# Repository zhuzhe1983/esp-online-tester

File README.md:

# ESP Online Tester

**Agent-configurable. Human-playable. Embeddable.**

A static platform for complete ESP32 products: select a device, attach accessories, load real firmware, play with its controls, and automate the same session. Forked from [mikroverk/esp32sim](https://github.com/mikroverk/esp32sim); the MIT-licensed Rust emulator runs locally in a browser through WebAssembly.

- [Open the platform](https://zhuzhe1983.github.io/esp-online-tester/platform/)
- [Platform guide and capability boundaries](docs/platform/README.md)
- [Coding-agent skill](skills/esp-online-tester/SKILL.md)
- [Contribute products, accessories and firmware](docs/platform/contributing.md)

Capability labels are product-specific. The [current platform guide](docs/platform/README.md) records implemented peripherals, verified firmware and remaining limits. A preview or successful configuration is not evidence that firmware ran.

The platform lives under `web/platform/`, shares the upstream emulator in `web/wasm/`, and needs no application server. Private DIY accessory definitions stay in the browser unless explicitly exported or shared. Public catalogs accept pull requests.

## LILYGO catalog coverage

The 127 existing LILYGO listings now have source-described 3D previews and newest-first ordering, with hardware dates, provisional storefront dates and unknown dates distinguished. There are 126 executable diagnostic or partial board configurations: 121 added profiles and five existing runtimes. T-Radar remains an A121 expansion module requiring an external host.

The 122 added models use 44 official CAD assemblies or parts and 78 approximate photograph-derived outlines. S2 and C5 currently support explicitly bounded SRAM applications; the P4 display remains a physical preview without DSI frame output. Diagnostic support does not establish factory firmware compatibility or physical model fit. See the [complete chronological inventory, source evidence and validation record](docs/platform/lilygo-adaptation-2026-11-22.md).

## Run locally

```sh
tools/wasm-build.sh
tools/fetch-demo-assets.sh --no-linux
python3 -m http.server 8080 --directory web
# Open http://localhost:8080/platform/
```

See the platform guide for remote firmware manifests, iframe integration, tests, and limitations. The original emulator interface remains available at `run.html`, and its demo gallery at `emulator.html`.

---

## Upstream emulator documentation

# esp32sim

esp32sim is an ESP32 emulator written in Rust. It runs real ESP32 firmware on your computer or in
a browser tab, without the hardware.

It boots the chip's own mask ROM, the real second-stage bootloader and your unmodified application.
It also models the board around the chip: displays, touch, LEDs, buttons, audio, camera and WiFi.

Try it in your browser, nothing to install: https://mikroverk.github.io/esp32sim/

`--chip esp32 --board ai-thinker-cam --cam-image image.ppm` supplies the AI-Thinker
ESP32-CAM's OV2640 with a BMP/PPM still image. Capture supports raw RGB565/YUV422
into internal DRAM at a fixed approximate 10 FPS; the usual JPEG+PSRAM
CameraWebServer path is unsupported. See the [camera scope and example](docs/esp32.md#the-camera---board-ai-thinker-cam).

## Supported chips

| Chip | CPU | Status | Boards |
| --- | --- | --- | --- |
| ESP32-S3 | 2 x Xtensa LX7 | mature | Atech 14-port kit, Waveshare Touch-LCD-4B, Touch-AMOLED-1.8, ESP32-S3-CAM |
| ESP32-S2 | 1 x Xtensa LX7 | SRAM diagnostics | three distinct LILYGO S2 profiles in the WASM platform; no ROM/MMU/SDK boot |
| ESP32-C3 | RISC-V RV32IMC | draft | console only |
| ESP32-C5 | 1 x RISC-V | SRAM diagnostics | Stamp-C5, LILYGO T7-C5 and T-Dongle-C5; no ROM/MMU/SDK boot |
| ESP32-C6 | RISC-V RV32IMAC | draft | Waveshare ESP32-C6-LCD-1.47 (with the 802.15.4 radio), Seeed XIAO ESP32-C6 |
| ESP32 (classic) | 2 x Xtensa LX6 | early | LilyGO TTGO T-Display, ESP32-2432S028 "Cheap Yellow Display", AI-Thinker ESP32-CAM (raw capture), Ulanzi TC001 |
| ESP32-P4 (rev < 3; rev ≥ 3: hello_world, ESP-Hosted) | 2 x RISC-V RV32IMAFC | draft | console only; the C6 co-processor over SDIO |
| ESP32-S31 | 2 x RISC-V RV32IMAFC | draft | native Machine CLI (`--chip s31`); IDF hello_world and ESP-Mosaico; Mosaico V1.2 in the WASM product platform |

S31 supports the native CLI and its `--web` board view, plus ESP-Mosaico V1.2 in
the WebAssembly product platform. The unchanged official Hello 0.1.3 recovery image
boots and responds to touch and AI standby/wake inputs. The publisher currently
blocks browser CORS, so download the complete BIN and import it locally. The model
is photo-derived with UNKNOWN internals; see the [verified scope and limitations](docs/platform/mosaico-runtime.md).
The earlier strict
`Bringup` diagnostic runner and its guest fixtures remain available separately under
`esp32s31::bringup`. See [the board models](docs/boards.md).

## Features

- The full boot chain: mask ROM, bootloader, FreeRTOS, then your app. No patched firmware.
- WiFi with the unmodified Espressif WiFi library. Firmware joins a virtual access point, gets
  DHCP, DNS and NTP, and can reach the real network, HTTPS included.
- Board models, so firmware can draw on a display, read touch, light LEDs and play sound.
- Speed: the S3 has a block cache and a JIT, and runs hello_world about 30 times faster than real
  time.
- A WebAssembly build of the same emulator for the browser.
- Comparisons with real chips: the S3 in JTAG lock-step, the C3 and C6 by console diff. See
  [hardware testing](docs/hardware-testing.md).

## Demos

These run on the [demo site](https://mikroverk.github.io/esp32sim/):

- Linux 6.11 on the ESP32-S3 ([svermigo/Linux-on-esp32-S3](https://github.com/svermigo/Linux-on-esp32-S3)), with a login shell.
- The Atech kit's Pocket Synth and its C64 SID jukebox ([atech-firmware](https://github.com/joakimeriksson/atech-firmware)).
- An LVGL touch panel at 480x480 with a SID player.
- [pocket-tank](https://github.com/mediacutlet/pocket-tank), where a small transformer model steers the fish.
- An 802.15.4 energy scanner, and two Contiki-NG motes running RPL/IPv6, on the ESP32-C6.
- MicroPython on a classic ESP32 T-Display.

You can also load your own firmware for any of the chips.

## Quick start

No Rust needed: the [releases](https://github.com/mikroverk/esp32sim/releases) carry prebuilt binaries
for macOS and Linux, and [docs/quick-start.md](docs/quick-start.md) takes your own build from the tarball
to a run in three steps. From a checkout:

```sh
cargo build --release
tools/fetch-demo-assets.sh --no-linux       # downloads the mask ROMs, which are not in the repo

FW=web/wasm/fw/public                       # demo firmware included in the repo
./target/release/esp32sim --boot rom --rom web/wasm/fw/esp32s3_rev0_rom.elf \
    --bootloader $FW/atech-bootloader.bin --ptable $FW/atech-ptable.bin --app $FW/atech-firmware.bin \
    --script $FW/atech-script1.txt --wav out.wav --tft-png tft.png --max-seconds 5
```

This boots the Atech synth firmware, plays a short script, and saves the audio to `out.wav` and
the display to `tft.png`. Use `esp32sim-c3`, `esp32sim-c6`, `esp32sim-p4`, `esp32sim-s31` or `--chip esp32` for the other chips.

[Getting started](docs/getting-started.md) covers the rest: your own ESP-IDF builds, each chip,
WiFi, scripts, the browser build and debugging.

## Documentation

- [Quick start](docs/quick-start.md): install the release, fetch the mask ROM, run your own build, read the result
- [Getting started](docs/getting-started.md): running firmware on each chip, WiFi, scripts, the browser build
- [CLI reference](docs/cli.md): every flag, environment variable and output file
- [Boards](docs/boards.md): what each board models, and how to add one
- [Architecture](docs/architecture.md): how the emulator is put together
- [Peripherals](docs/peripherals.md): which hardware blocks are modelled, and how completely
- [Hardware testing](docs/hardware-testing.md): how the emulator is compared with real chips
- [All documents](docs/README.md): chip notes, design decisions and plans

## Contributing

Bug fixes, peripherals, boards and new chips are welcome. [CONTRIBUTING.md](CONTRIBUTING.md) lists
what a pull request needs; these are the same checks CI runs. Security problems go through
[SECURITY.md](SECURITY.md), not the public issue tracker.

## Credits and license

esp32sim is released under the [MIT License](LICENSE).

Authors: Joakim Eriksson, RISE ([@joakimeriksson](https://github.com/joakimeriksson)),
Alice ([@aliceisjustplaying](https://github.com/aliceisjustplaying)) and
Mattia Fiumara, Schematik ([@mfiumara](https://github.com/mfiumara)), together with
[other contributors](https://github.com/mikroverk/esp32sim/graphs/contributors).

The emulator was written from the ESP-IDF register headers, the Xtensa core configuration that
ships with ESP-IDF, the RISC-V specification, the chips' technical reference manuals and observed
firmware behaviour. QEMU was consulted only to confirm instruction semantics; no code was copied.

esp32sim is unofficial and not affiliated with Espressif Systems.

Third-party code, data and demo files keep their own licenses:

- pocket-tank ([mediacutlet/pocket-tank](https://github.com/mediacutlet/pocket-tank), MIT). Its
  bootloader, partition table and app are in `web/wasm/fw/public/` with `pocket-tank-LICENSE.txt`;
  its model is downloaded.
- MicroPython ([micropython.org](https://micropython.org/download/ESP32_GENERIC/), MIT): the
  official ESP32_GENERIC v1.29.0 image used by the T-Display demo, downloaded by
  `tools/fetch-micropython.sh` and not in the repo. The demo's app and filesystem are in
  `examples/ttgo-tdisplay`, with Russ Hughes's st7789py driver and fonts (MIT); the notice is in
  `web/wasm/fw/public/tdisplay-NOTICE.txt`.
- Mask ROM ELFs ([espressif/esp-rom-elfs](https://github.com/espressif/esp-rom-elfs), Apache-2.0),
  downloaded, not in the repo.
- xterm.js ([xtermjs/xterm.js](https://github.com/xtermjs/xterm.js), MIT), downloaded, not in the repo.
- The Linux image ([svermigo/Linux-on-esp32-S3](https://github.com/svermigo/Linux-on-esp32-S3),
  GPL-3.0), downloaded, not in the repo.
- ESP-IDF ADC calibration data (Espressif, Apache-2.0): the curve-fitting coefficients and S3 ADC1
  calibration from #165, in `esp-periph/src/sar_adc.rs`; see `esp-periph/LICENSE-ADC`.

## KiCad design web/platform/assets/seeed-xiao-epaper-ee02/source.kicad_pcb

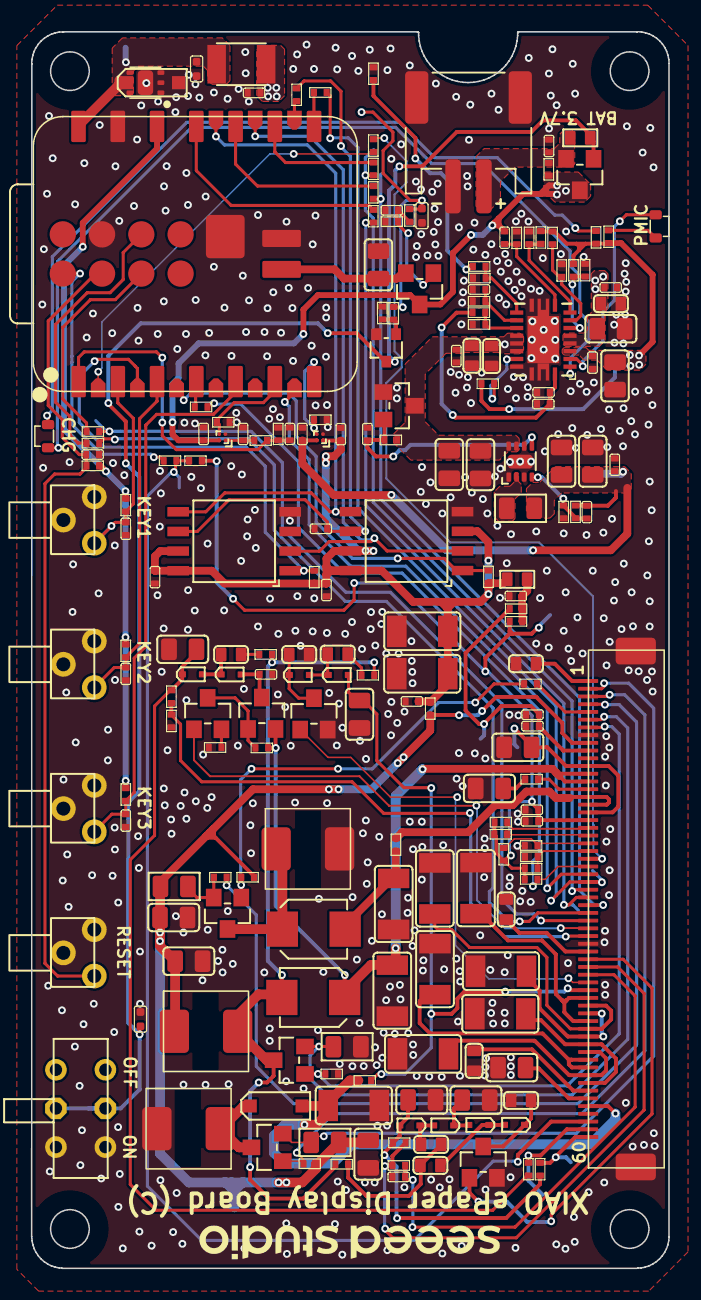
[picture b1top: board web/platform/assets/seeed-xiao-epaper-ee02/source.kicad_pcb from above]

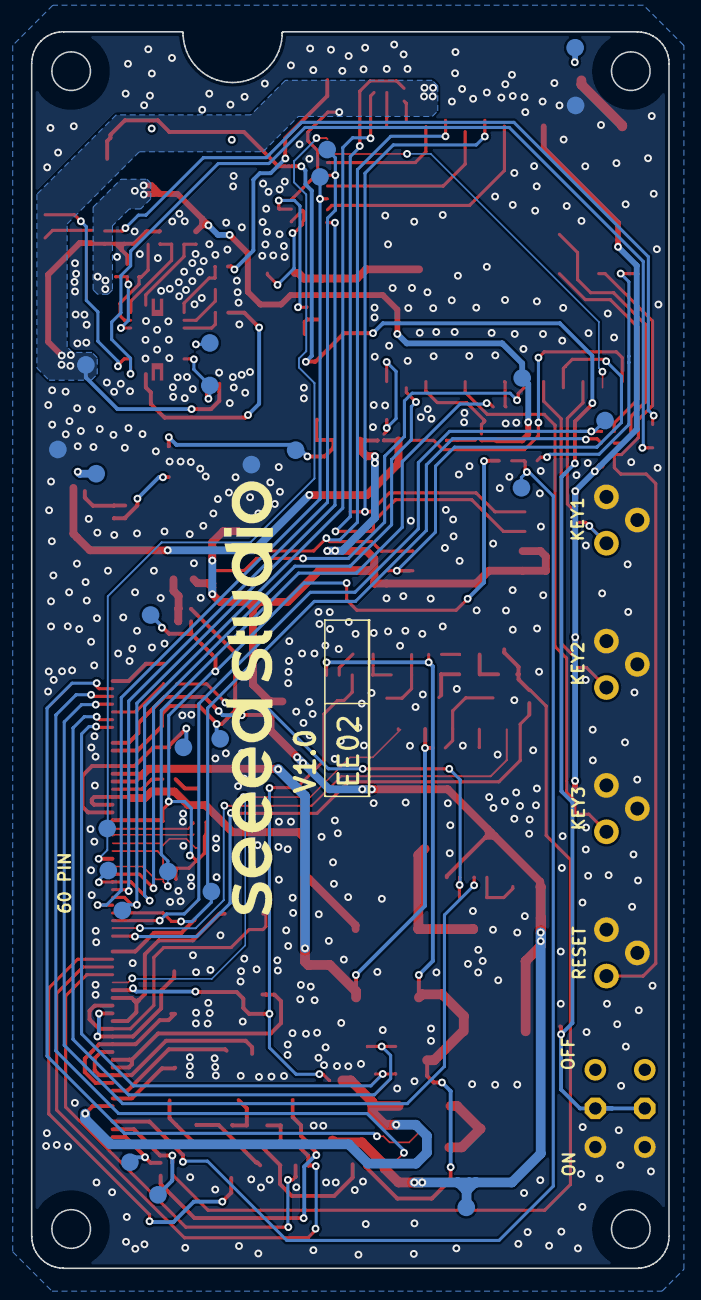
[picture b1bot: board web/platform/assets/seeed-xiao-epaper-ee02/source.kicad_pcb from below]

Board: 2 copper layers, 41.2 x 80.0 mm, 225 parts (25 on the bottom side), 123 nets.

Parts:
C1, C12, C14: 10uF; C1206
C2, C7, C9, C13, C15, C16, C24: 4.7uF,50V; C0805
C3: 470nF; C0402
C4, C20, C23, C28, C36, C44, C49, C50, C51, C53, C54, C55, C56, C58, C61, C63, C64, C71: 100nF; C0402
C5, C68: 100uF; C1206
C6, C8, C17, C19, C27, C52, C66: 470nF; C0603
C10, C21: 47nF; C0603
C11, C40, C41, C42, C43, C60, C72: 10uF; C0805
C18: 1uF; C0805
C22: 220nF,50V; C0402
C25, C39, C46, C47, C48, C59: 1uF; C0402
C26, C29: 10uF; C0402
C30, C31, C32, C33, C34, C65: 47uF,25V; C1206
C35, C70: 22uF; C0805
C37, C38, C57: 10uF; C0603
C45: 22pF; C0402
C62: 1nF; C0402
C67: 220nF; C0402
C69: 10nF; C0402
C73: 47pF; C0402
D1, D3, D6, D7, D8, D9, D10, D11: LRB520S-30T1G; SOD-523
D2, D4: MBRS240LT3; DO-214AA_SMB
D5, D16: Green; LED2-0.6X1.7MM
D12: SMF5.0CA; SOD-123
D13, D14, D15: TPD1E10B06DPYR; ESD-0402
D17: 1N5819HW; SOD-123
F1: 2A; F1210
FB1: MPZ1608S221ATA00; L0603
J1: 130-221-600003-W3G; FPC60-0.5-33.5X4.9X2MM
J3: A2001WF-02A; JST2+2P_2.0_PH_S2B-PH-SM4-TB_1x02-1MP_Horizontal
L2: 0.47uH; L0805
L3, L4, L5: 15uH; L5.5X5.2X3MM
Q1, Q3, Q6, Q10: CJ3407; SOT23
Q2, Q5: 30V 5.8A; SOT23
Q4: LBSS138WT1G; SOT-323
Q7: MMBT3906LT3G; SOT-23
Q8, Q9: 40V,200mA; SOT-23
R1, R6, R55: 1M; R0402
R2, R5, R7, R10, R12, R18, R21, R25, R32, R44, R45, R46, R54, R57, R60, R62, R65, R66, R67: 0R; R0402
R3, R8, R23: 0.2R; R0805
R4, R43, R61, R68, R78: 22R; R0402
R9, R26, R27, R40, R56, R74, R75: 100K; R0402
R11, R17, R19, R28, R29, R30, R31, R35, R36, R37, R38, R39, R63, R64, R70, R71, R72, R73, R76: 10K; R0402
R13, R42, R69: 4.7K; R0402
R14, R15, R47: 2K; R0402
R16, R22: 1K; R0402
R20: NCP15XH103F03RC; R0402
R24: 22K; R0402
R33: 80.6K; R0402
R34: 100K; R0603
R41: 3.57K; R0402
R48: 1.5K; R0402
R49, R51, R53: 2.2R; R0402
R50: 110K; R0402
R52: 16k; R0402
R58: 402K; R0402
R59: 4.3k; R0402
R77: 36K; R0402
SW1: MK-22D18 G3; SW6-2CH-2.54-9X3.5X3.5
SW2, SW3, SW4, SW5: EL-4501V; SW3-DIP-SIDE-4.5X4.5X5.5MM
TP1, TP2, TP3, TP4, TP5, TP6, TP7, TP8, TP9, TP10, TP11, TP12, TP13, TP14, TP15, TP16, TP17, TP18, TP19, TP20, TP21, TP23, TP25, TP26, TP27: Test Point; TP-D45MIL
U1: BQ24070RHLR; RHL20_2P05X3P05
U3: XIAO-HALF-HOLE-33P; XIAO-ESP32-S3-Plus-SMD
U4: ME2805A293XG; SOT-23
U5: ZB25VQ32DSJG; SOIC8-1.27-5.3X5.3MM
U6: GT32L32S0140; SOIC8-1.27-5.3X5.3MM
U7: TVS0500DRVR; WSON7-0.65-2X2X0.8MM
U8: TPS62065DSGR; DFN8G-0.5-2X2MM
U16, U17: TPS22916CYFPR; WLCSP4-0.4-0.77X0.77X0.33MM

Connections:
+3.3V: C42.2, C43.2, C44.1, C45.1, C46.1, L2.2, R56.2, TP6.1 (T), U16.A2 (VIN)
/E-ink/DRVN: J1.37, Q8.1 (B)
/E-ink/DRVN2: J1.40, Q9.1 (B)
/E-ink/DRVP_G: J1.33, Q5.1 (G)
/E-ink/FBN: J1.38, R52.2, R58.1
/E-ink/FBP: J1.34, R50.2, R59.1
/E-ink/GDRC: J1.3, Q6.1 (G), R55.1
/E-ink/GDRN: J1.5, R65.1
/E-ink/GDRP: J1.7, Q2.1 (G), R6.2
/E-ink/LX: D2.1, L5.2, Q2.3 (D), R49.2, R51.2, R53.2
/E-ink/REG_VGN: C25.1, J1.39, R52.1
/E-ink/RESEC: J1.2, Q6.2 (S), R8.1
/E-ink/RESEN: J1.4, R7.1
/E-ink/RESEP: J1.6, Q2.2 (S), R3.2
/E-ink/VBB_3P5V: C12.2, D17.1, J1.56, R57.1
/E-ink/VCC: C11.2, J1.12, J1.18, TP17.1 (T)
/E-ink/VDDN: J1.16, J1.17, R5.2
/E-ink/VDDP: C14.1, D2.2, J1.13, J1.14, Q7.2 (E), R9.1
/E-ink/VGH: J1.59, R66.2, TP16.1 (T)
/E-ink/VGL: J1.60, R67.2, TP15.1 (T)
/E-ink/VNCP_3P5V: C7.2, D11.1, J1.41, R57.2
/XIAO/BUTON1: C54.1, R36.1, SW3.2, U3.2 (GPIO2_D1/A1)
/XIAO/BUTON2: C55.1, R37.1, SW4.2, U3.3 (GPIO3_D2/A2)
/XIAO/BUTON3: C56.1, R38.1, SW5.2, U3.5 (GPIO5_D4/A4/I2C_SDA)
/XIAO/RST: C53.1, R35.1, SW2.2, U3.26 (EN)
/XIAO/SPI1_CLK: C73.1, R78.2, U5.6 (CLK), U6.6 (CLK)
/XIAO/SPI1_CS0: R39.1, U3.16 (GPIO39_CAM_SCL/I2S_SCK), U6.1 (/CS)
/XIAO/SPI1_CS1: R31.1, U3.17 (GPIO40_CAM_SDA/I2S_WS), U5.1 (/CS)
/XIAO/SPI1_MISO: U3.22 (GPIO12_DVP_Y7/SPI_MISO1), U5.2 (DO(IO1)), U6.2 (DO(IO1))
/XIAO/SPI1_MOSI: U3.23 (GPIO13_DVP_PCLK/SPI_SCK1), U5.5 (DI(IO0)), U6.5 (DI(IO0))
ADC_EN: R27.2, U3.6 (GPIO6_D5/A5/I2C_SCL), U17.B2 (EN)
AVDD: C9.2, C13.2, C16.2, J1.9, L5.1, R1.2, R2.2, R8.2, R23.2, R55.2, TP9.1 (T)
BAT_ADC: C62.1, R28.1, R29.2, U3.1 (GPIO1_D0/A0)
EDP_BUSY: J1.25, R47.1, R62.1, TP26.1 (T)
EDP_DC: J1.26, U3.20 (GPIO10_XMCLK/ADC_BAT)
EDP_RST: J1.24, R43.1, TP25.1 (T)
GND: C1.2, C2.1, C3.1, C4.2, C5.2, C7.1, C9.1, C10.2, C11.1, C12.1, C13.1, C14.2, C15.1, C16.1, C18.1, C20.1, C21.2, C22.2, C23.1, C24.1, C25.2, C26.1, C27.1, C28.1, C29.1, C30.1, C31.1, C32.1, C33.1, C34.1, C35.2, C36.2, C37.2, C38.2, C39.2, C40.1, C41.1, C42.1, C43.1, C44.2, C46.2, C47.2, C48.2, C49.2, C50.2, C51.2, C52.1, C53.2, C54.2, C55.2, C56.2, C57.2, C58.2, C59.2, C60.1, C61.2, C62.2, C63.2, C64.2, C65.1, C66.1, C68.2, C69.2, C70.2, C71.2, C72.1, C73.2, D12.1, D13.1, D14.1, D15.1, J1.8, J1.35, J1.61, J1.62, J3.2, J3.3, J3.4, L3.2, L4.2, Q4.2 (S), Q8.2 (E), Q9.2 (E), R3.1, R6.1, R14.2, R15.2, R20.1, R21.1, R24.1, R26.1, R27.1, R29.1, R33.1, R40.1, R41.1, R48.1, R59.2, R71.1, R73.1, R75.1, R76.1, R77.1, SW1.CH1B, SW1.CH2B, SW2.1, SW2.3 (GND), SW3.1, SW3.3 (GND), SW4.1, SW4.3 (GND), SW5.1, SW5.3 (GND), TP4.1 (T), TP5.1 (T), TP8.1 (T), U1.11 (VSS), U1.19 (GND), U1.20 (GND), U1.21 (EPAD), U3.13 (GND), U3.27 (GND1), U3.33 (GND2), U3.34 (PAD), U4.1 (VSS), U5.4 (GND), U6.4 (GND), U7.1 (GND), U7.2 (GND1), U7.3 (GND2), U7.7 (PAD), U8.1 (PGND), U8.3 (AGND), U8.6 (MODE), U8.9 (PAD), U16.B1 (GND), U17.B1 (GND)
unnamed: C1.1, D4.1, R5.1
unnamed: C2.2, D7.1, R58.2, R67.1
unnamed: C6.1, D9.2, D10.1
unnamed: C6.2, R49.1
unnamed: C8.1, D8.1, D11.2
unnamed: C8.2, R53.1
unnamed: C15.2, D10.2, R50.1, R66.1
unnamed: C17.1, D6.1, D7.2
unnamed: C17.2, C19.2, R51.1
unnamed: C18.2, D3.1, D6.2
unnamed: C19.1, D1.1, D3.2
unnamed: C24.2, J1.55
unnamed: C27.2, J1.1
unnamed: C30.2, J1.42, J1.45
unnamed: C31.2, J1.43, J1.46
unnamed: C32.2, J1.49, J1.52
unnamed: C33.2, J1.50, J1.51
unnamed: C34.2, J1.44, J1.47
unnamed: C52.2, J1.54
unnamed: C64.1, FB1.2, R10.1, R12.1
unnamed: C65.2, J1.48, J1.53
unnamed: C66.2, J1.36
unnamed: C72.2, R46.1
unnamed: D5.1 (+), R19.1
unnamed: D5.2 (-), U1.3 (STAT2)
unnamed: D16.1 (+), R17.1
unnamed: D16.2 (-), U1.2 (STAT1)
unnamed: J1.15, R46.2
unnamed: J1.20, R63.2
unnamed: J1.21, R64.2
unnamed: J1.22, R13.1, R14.1
unnamed: J1.23, R15.1, R42.1
unnamed: D4.2, L3.1, Q1.3 (D)
unnamed: Q1.1 (G), R1.1, R65.2
unnamed: Q1.2 (S), R7.2, R23.1
unnamed: D15.2, Q3.1 (G), Q4.3 (D), R34.2, SW1.COM1, SW1.COM2
unnamed: C39.1, J3.1, Q3.2 (S), R32.2, R34.1
unnamed: Q4.1 (G), R16.2, R40.2
unnamed: Q5.3 (D), Q7.1 (B), R9.2
unnamed: Q5.2 (S), R48.2
unnamed: D17.2, L4.1, Q6.3 (D)
unnamed: C22.1, D9.1, Q7.3 (C)
unnamed: C21.1, D1.2, Q8.3 (C)
unnamed: C10.1, D8.2, Q9.3 (C)
unnamed: C59.1, Q10.1 (G), R30.2, R75.2
unnamed: C60.2, Q10.2 (S), U3.32 (VBAT)
unnamed: R18.1, R20.2
unnamed: D12.2, D13.2, F1.1, TP7.1 (T), U3.14 (VBUS), U7.4 (IN), U7.5 (IN2), U7.6 (IN2)
unnamed: R11.1, TP18.1 (T), U1.18 (~PG)
unnamed: C51.1, R25.1, TP20.1 (T), U4.2 (VOUT), U8.5 (EN)
unnamed: R70.2, R71.2, U1.9 (CE)
unnamed: C69.1, R77.2, U1.13 (DPPM)
unnamed: C67.2, R41.2, U1.10 (ISET1)
unnamed: R74.1, R76.2, U1.7 (ISET2)
unnamed: R72.2, R73.2, U1.8 (MODE)
unnamed: R22.2, R33.2, U1.14 (TMR)
unnamed: R18.2, R21.2, U1.12 (TS)
unnamed: R62.2, U3.4 (GPIO4_D3/A3)
unnamed: R4.1, U3.9 (GPIO7_D8/A8/SCK)
unnamed: R44.1, U3.10 (GPIO8_D9/A9/MISO)
unnamed: R45.1, U3.11 (GPIO9_D10/A10/MOSI)
unnamed: R78.1, U3.21 (GPIO11_DVP_Y8/SPI_MOSI1)
unnamed: R43.2, U3.15 (GPIO38_DVP_VSYNC/I2S_SD)
unnamed: R60.1, U3.29 (MTCK/IO39/CAM_SCL/I2S_SCK)
unnamed: R68.1, U3.24 (MTDI/IO41/PDM_DATA/RX1)
unnamed: R54.1, U3.28 (MTMS/IO42/PDM_CLK/TX1)
unnamed: R61.1, U3.8 (U0RXD_D7/RX)
unnamed: C45.2, R24.2, R56.1, U8.4 (FB)
unnamed: L2.1, U8.2 (SW)
unnamed: C49.1, R28.2, U17.A1 (VOUT)
PWR_EN: R26.2, U3.7 (U0TXD_D6/TX), U16.B2 (EN)
SPIO_CLK: J1.28, R4.2, TP10.1 (T)
SPIO_CS_M: J1.27, R61.2, TP27.1 (T)
SPIO_CS_S: J1.58, R68.2, R69.1, TP23.1 (T)
SPIO_D0: J1.29, R45.2, TP11.1 (T)
SPIO_D1: J1.30, R44.2, TP12.1 (T)
SPIO_D2: J1.31, R60.2, TP13.1 (T)
SPIO_D3: J1.32, R54.2, TP14.1 (T)
VBAT: C35.1, C36.1, C37.1, C48.1, C67.1, Q3.3 (D), Q10.3 (D), R32.1, TP3.1 (T), U1.5 (BAT), U1.6 (BAT), U17.A2 (VIN)
VBUS: C58.1, C70.1, C71.1, D14.2, F1.2, R11.2, R16.1, R17.2, R19.2, R30.1, R70.1, R72.1, R74.2, TP21.1 (T), U1.4 (IN)
VCC_3V3: C4.1, C5.1, C47.1, C50.1, C63.1, C68.1, FB1.1, R2.1, R31.2, R39.2, U5.3 (/WP(IO2)), U5.7 (/HOLD(IO3)), U5.8 (VCC), U6.7 (/HOLD(IO3)), U6.8 (VCC), U16.A1 (VOUT)
VDD: C20.2, C26.2, J1.10, R10.2, TP1.1 (T)
VDDIO: C28.2, C29.2, J1.19, R12.2, R13.2, R42.2, R47.2, R63.1, R64.1, R69.2, TP2.1 (T)
VREF: C3.2, C23.2, R22.1, U1.1 (VREF)
VSYS: C38.1, C40.2, C41.2, C57.1, C61.1, R25.2, TP19.1 (T), U1.15 (OUT), U1.16 (OUT), U1.17 (OUT), U4.3 (VIN), U8.7 (AVIN), U8.8 (PVIN)
XIAO_3V3: R35.2, R36.2, R37.2, R38.2, U3.12 (VCC_3V3)

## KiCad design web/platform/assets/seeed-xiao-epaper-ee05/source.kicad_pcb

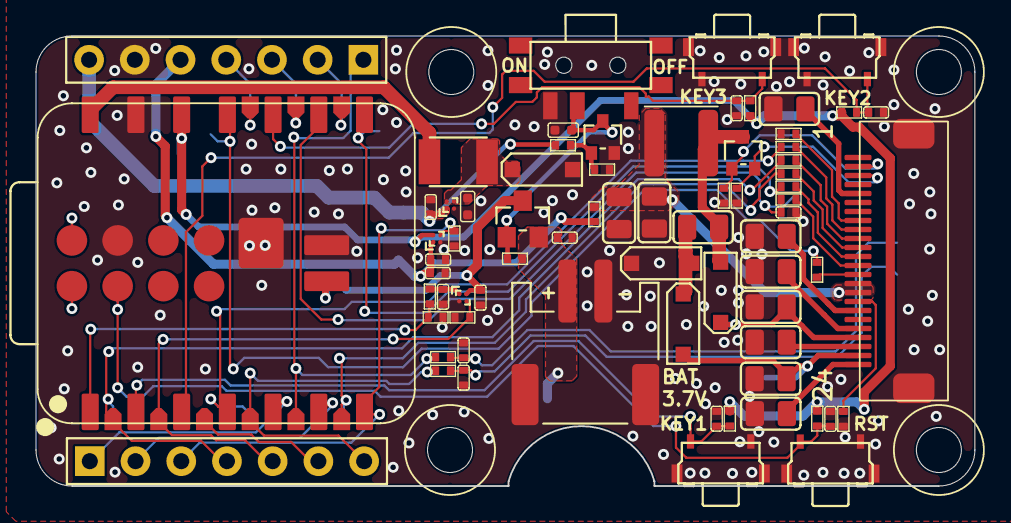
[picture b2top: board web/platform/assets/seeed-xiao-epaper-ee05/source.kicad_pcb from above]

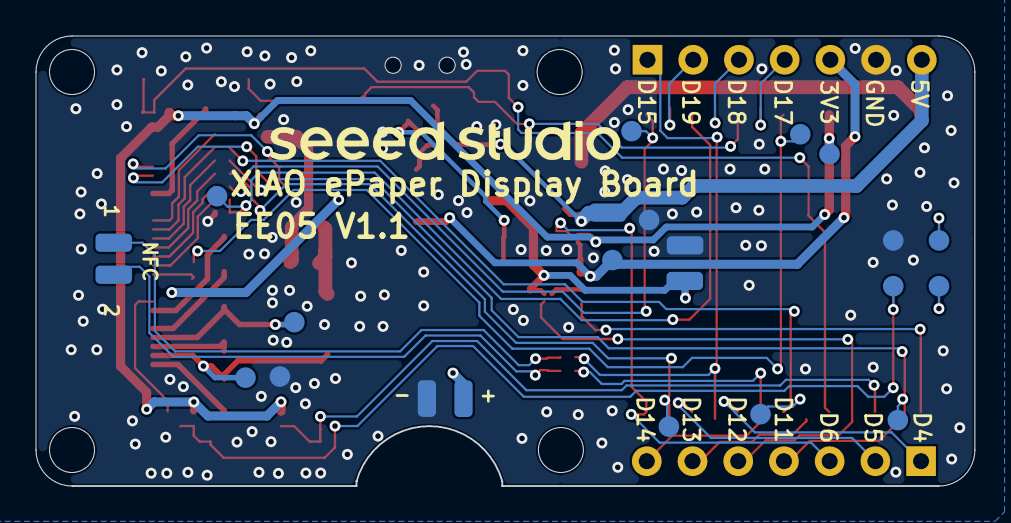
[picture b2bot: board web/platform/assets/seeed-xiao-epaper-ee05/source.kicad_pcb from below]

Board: 2 copper layers, 52.2 x 25.0 mm, 99 parts (23 on the bottom side), 56 nets.

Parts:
C1: 10uF; C0805
C2, C3, C4: 1uF; C0805
C5, C6, C7, C17, C18, C19: 4.7uF; C0805
C8, C9, C11, C12, C13, C14, C15: 100nF; C0402
C10, C16, C20: 1uF; C0402
C21: 33pF; C0402
C64, C65: 300pF; C0402
D1, D2, D3: MBR0530; SOD-123
D6, D15: TPD1E10B06DPYR; ESD-0402
D7: SMF5.0CA; SOD-123
F1: 2A; F1210
J1: FPC 24P TOP contact; FPC24-0.5-15.5X4.9X2MM
J2, J4: ST-PH-254-0087-1*7P-PC1.8; H7-2.54
J3: A2001WF-02A; JST2+2P_2.0_PH_S2B-PH-SM4-TB_1x02-1MP_Horizontal
K1, K2, K3, K4: TD-1100SN-A4N-S1R; SW4-SMD-4.5X3.8X1.8MM-90D
L1: 47uH ±20% 570mA; L4018
Q3: CJ3407; SOT23
Q4: LBSS138WT1G; SOT-323
Q5: 30V-1.4A; SOT-323
R1, R9, R10, R15, R16, R17, R18, R20, R24: 0R; R0402
R2, R4, R11, R21: 1M; R0402
R3, R5, R6, R7, R8, R12, R22, R23: 10K; R0402
R13: 100K; R0402
R14: 2.2R; R0402
R19: 22R; R0402
SW6: MSK-12C02 ZD; SW7-SMD-6.7X2.6X1.4MM-90D
TP1, TP2, TP3, TP4, TP5, TP7, TP8: Test Point; TP-80X40MIL
TP6, TP9, TP10, TP11, TP12, TP13, TP14, TP15, TP16, TP17, TP18, TP19, TP20, TP21, TP22, TP23: Test Point; TP-D45MIL
U1, U2, U6, U7, U8: LOGO_CC_BY-SA_4.0
U3: XIAO-ESP32-S3-Plus-SMD
U4, U5, U9: TPS22916CNYFPR; WLCSP4-0.4-0.77X0.77X0.33MM

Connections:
+3.3V: R5.2, R6.2, R7.2, R8.2, TP6.1 (T_1), U3.12 (3V3_OUT), U4.A2 (VIN)
ADC_EN: J2.5, R21.2, U3.16 (D12), U9.B2 (EN)
BAT_ADC: R22.1, R23.2, U3.1 (D0)
BOTTON1: C13.1, K2.2, R7.1, U3.2 (D1)
BOTTON2: C12.1, K3.2, R6.1, U3.3 (D2)
BOTTON3: C9.1, K4.2, R5.1, U3.10 (D9)
BS1: J1.17, R12.2
EDP_BUSY: R15.1, TP13.1 (T_1), U3.4 (D3)
EDP_DC: R17.1, TP15.1 (T_1), U3.20 (D16)
EDP_RES: J2.4, R16.1, TP14.1 (T_1), U3.15 (D11)
GDR: J1.23, Q5.1 (G), R13.2
GND: C1.2, C2.2, C3.2, C4.2, C5.2, C6.2, C8.2, C9.2, C10.2, C11.2, C12.2, C13.2, C14.2, C15.2, C16.2, C17.2, C18.2, C19.2, C20.2, C21.2, C64.1, C65.2, D2.2, D6.1, D7.1, D15.1, J1.25, J1.26, J3.2, J3.3, J3.4, J4.6, K1.1, K1.3 (S1), K1.4 (S2), K2.1, K2.3 (S1), K2.4 (S2), K3.1, K3.3 (S1), K3.4 (S2), K4.1, K4.3 (S1), K4.4 (S2), Q4.2 (S), R4.1, R11.1, R12.1, R13.1, R14.1, R21.1, R23.1, R24.1, SW6.3 (B), TP3.1 (T_1), TP8.1 (T_1), TP9.1 (T_1), TP12.1 (T_1), TP23.1 (T_1), U3.13 (GND), U3.27 (GND), U3.33 (GND), U3.34 (PAD), U4.B1 (GND), U5.B1 (GND), U9.B1 (GND)
GPIO05_D4/A4/I2C_SDA: J2.1, U3.5 (D4)
GPIO06_D5/A5/I2C_SCL: J2.2, U3.6 (D5)
GPIO11_D19/SPI1_MOSI: J4.2, U3.21 (D19)
GPIO12_D18/SPI1_MISO: J4.3, U3.22 (D18)
GPIO13_D17/SPI1_SCK: J4.4, U3.23 (D17)
GPIO40_D13/I2S_WS/MTDO: J2.6, U3.17 (D13)
unnamed: C7.1, D1.2, D2.1
unnamed: J1.8, R24.2
unnamed: J1.11, R20.2
unnamed: J1.12, R19.2
unnamed: J1.13, R18.2
unnamed: J1.14, R17.2
unnamed: J1.15, R16.2
unnamed: J1.16, R15.2
unnamed: D15.2, Q3.1 (G), Q4.3 (D), R2.1, SW6.2 (COM)
unnamed: C10.1, J3.1, Q3.2 (S), R2.2, TP4.1 (T_1)
unnamed: Q4.1 (G), R3.1, R4.2
unnamed: C7.2, D3.1, L1.2, Q5.3 (D)
unnamed: C65.1, R10.2, TP1.1 (T_1)
unnamed: C64.2, R9.2, TP2.1 (T_1)
unnamed: TP20.1 (T_1), U3.24 (D14/MTDI)
unnamed: TP21.1 (T_1), U3.25 (D13/MTDO)
unnamed: F1.1, U3.14 (VBUS)
unnamed: D6.2, D7.2, F1.2, U5.A2 (VIN), U5.B2 (EN)
unnamed: C14.1, R22.2, U9.A1 (VOUT)
PWR_EN: J2.3, R11.2, U3.7 (D6), U4.B2 (EN)
RESEH: J1.22, Q5.2 (S), R14.2
RST: C15.1, K1.2, R8.1, TP22.1 (T_1), U3.26 (EN)
RX1/NFC1: J2.7, R9.1, U3.18 (D14)
SPI0_CS: R18.1, TP16.1 (T_1), U3.8 (D7)
SPI0_MOSI: R20.1, TP18.1 (T_1), U3.11 (D10)
SPI0_SCL: C21.1, R19.1, TP17.1 (T_1), U3.9 (D8)
TX1/NFC2: J4.1, R10.1, U3.19 (D15)
VBAT: C20.1, Q3.3 (D), TP5.1 (T_1), U3.32 (VBAT), U9.A2 (VIN)
VBUS: C11.1, J4.7, R3.2, TP7.1 (T_1), U5.A1 (VOUT)
VCC_3V3: C8.1, C16.1, J4.5, R1.1, TP19.1 (T_1), U4.A1 (VOUT)
VCI: C1.1, C2.1, J1.9, J1.10, L1.1, R1.2
VCOM: C4.1, J1.1
VDD: C3.1, J1.7
VGH: C6.1, D3.2, J1.4, TP10.1 (T_1)
VGL: C5.1, D1.1, J1.2, TP11.1 (T_1)
VSH1: C18.1, J1.5
VSH2: C17.1, J1.20
VSL: C19.1, J1.3
